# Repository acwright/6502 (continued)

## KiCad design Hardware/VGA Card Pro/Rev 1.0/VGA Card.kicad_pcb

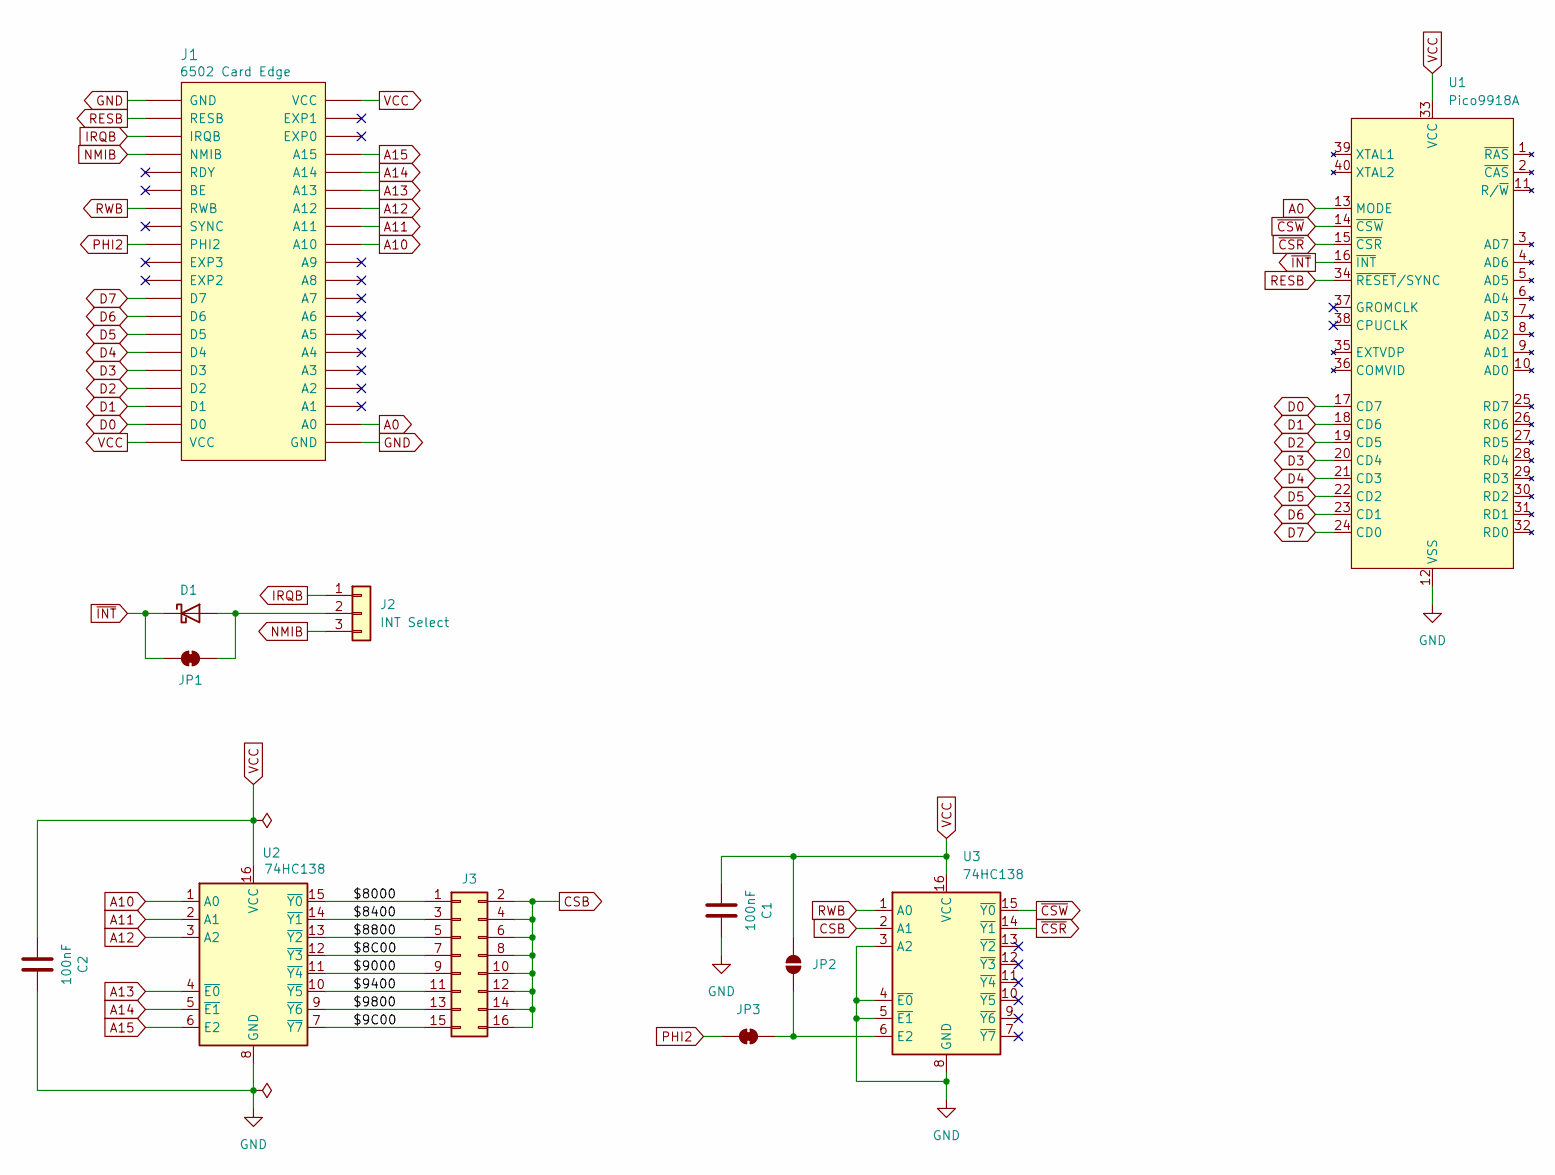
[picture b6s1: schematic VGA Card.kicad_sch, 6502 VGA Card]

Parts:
C1, C2: 100nF; C_0805_2012Metric; LCSC C49678
D1: D_Schottky; D_DO-35_SOD27_P7.62mm_Horizontal
J1: 6502 Card Edge
J2: INT Select; PinHeader_1x03_P2.54mm_Vertical
J3: Conn_02x08_Odd_Even; PinHeader_2x08_P2.54mm_Vertical
JP1, JP3: SolderJumper_2_Bridged; SolderJumper-2_P1.3mm_Bridged_RoundedPad1.0x1.5mm
JP2: SolderJumper_2_Open; SolderJumper-2_P1.3mm_Open_RoundedPad1.0x1.5mm
U1: Pico9918A; DIP-40_W15.24mm_LongPads
U2, U3: 74HC138; SOIC-16_3.9x9.9mm_P1.27mm; LCSC C5602

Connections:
/$8C00: J3.7, U2.12 (~Y3)
/$9C00: J3.15, U2.7 (~Y7)
/$8000: J3.1, U2.15 (~Y0)
/$8400: J3.3, U2.14 (~Y1)
/$8800: J3.5, U2.13 (~Y2)
/$9000: J3.9, U2.11 (~Y4)
/$9400: J3.11, U2.10 (~Y5)
/$9800: J3.13, U2.9 (~Y6)
A0: J1.A0, U1.13 (MODE)
A10: J1.A10, U2.1 (A0)
A11: J1.A11, U2.2 (A1)
A12: J1.A12, U2.3 (A2)
A13: J1.A13, U2.4 (~E0)
A14: J1.A14, U2.5 (~E1)
A15: J1.A15, U2.6 (E2)
CSB: J3.2, J3.4, J3.6, J3.8, J3.10, J3.12, J3.14, J3.16, U3.2 (A1)
D0: J1.D0, U1.17 (CD7)
D1: J1.D1, U1.18 (CD6)
D2: J1.D2, U1.19 (CD5)
D3: J1.D3, U1.20 (CD4)
D4: J1.D4, U1.21 (CD3)
D5: J1.D5, U1.22 (CD2)
D6: J1.D6, U1.23 (CD1)
D7: J1.D7, U1.24 (CD0)
GND: C1.2, C2.2, J1.GND, U1.12 (VSS), U2.8 (GND), U3.3 (A2), U3.4 (~E0), U3.5 (~E1), U3.8 (GND)
IRQB: J1.IRQB, J2.1
NMIB: J1.NMIB, J2.3
unnamed: D1.2 (A), J2.2, JP1.2 (B)
unnamed: JP2.2 (B), JP3.1 (A), U3.6 (E2)
PHI2: J1.PHI2, JP3.2 (B)
RESB: J1.RESB, U1.34 (~RESET/SYNC)
RWB: J1.RWB, U3.1 (A0)
VCC: C1.1, C2.1, J1.VCC, JP2.1 (A), U1.33 (VCC), U2.16 (VCC), U3.16 (VCC)
~CSR: U1.15 (~CSR), U3.14 (~Y1)
~CSW: U1.14 (~CSW), U3.15 (~Y0)
~INT: D1.1 (K), JP1.1 (A), U1.16 (~INT)

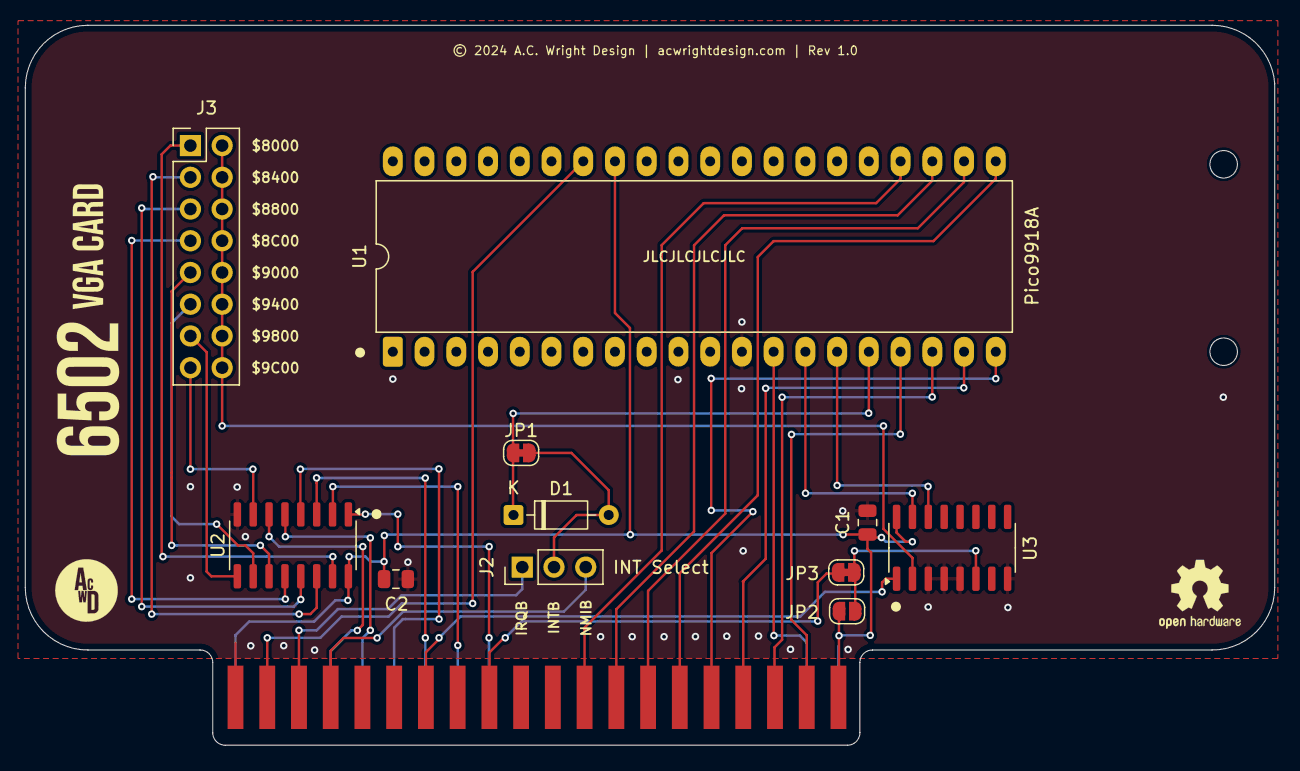
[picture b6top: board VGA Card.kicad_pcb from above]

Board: 2 copper layers, 100.0 x 57.6 mm, 12 parts (0 on the bottom side), 36 nets.
